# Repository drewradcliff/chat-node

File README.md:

# chat-node

A small USB-C-powered Wi-Fi voice puck for the kitchen or living room: one microphone, one speaker, one big
lit button. It is a thin audio client. It streams microphone audio to a gateway on a Mac mini over a
WebSocket and plays what the gateway streams back. No AI model and no third-party keys live on the device.

| Folder | What is in it |
|---|---|
| `boards/chat-node/` | KiCad project of the main board (schematic, layout, project library) and the scripts that generate it |
| `mfg/chat-node/` | Generated manufacturing set: Gerbers, drill, BOM, placement, schematic PDF, check reports. Never edit by hand |
| `mech/` | 3D-printed enclosure: FreeCAD scripts, STEP files, renders, fit-check log |
| `firmware/` | ESP-IDF firmware and the wire protocol (`PROTOCOL.md`). Not yet compiled or run on hardware |
| `gateway/` | Small Python bring-up server (echo and tone modes). Not the real gateway, no AI |

## Hardware in brief

- ESP32-S3-WROOM-1-N16R8 (16 MB flash, 8 MB PSRAM, built-in antenna), native USB for flashing and console.
- TDK ICS-43434 I2S microphone; MAX98357A I2S Class-D amplifier into a 40 mm, 4 ohm, 3 W speaker.
- Mic and amplifier are on separate I2S ports, so full duplex can be tried later without a board change.
- Kailh Choc V1 keyboard switch as the main button, lit from below by one SK6812MINI-E RGB LED.
- USB-C, 5 V only: 5.1k on each CC pin, 2 A resettable fuse, ESD array on the data lines, 3.3 V LDO.
- Board: 48 x 37 mm, 2 layers, all assembled parts on one side.

The board hangs under the lid with its component side facing DOWN. The bare back of the board faces the lid:
the microphone listens up through a hole in the board, the LED shines up through a slot, and the switch
stands on the back of the board under the button cap.

| Function | GPIO |
|---|---|
| Mic SCK / WS / SD (I2S0) | 11 / 13 / 14 |
| Amp SD_MODE / DIN / BCLK / LRCLK (I2S1) | 4 / 5 / 6 / 7 |
| Main button (to GND) | 15 |
| Status LED data | 16 |
| USB D- / D+ | 19 / 20 |
| BOOT button | 0 |
| Free | 8, 9, 10, 12, 17, 18 |

Test pads on the component side: 5V, 3V3, GND, EN, mic SD, mic SCK, amp DIN.

## The board files are generated

`chat-node.kicad_sch` and `chat-node.kicad_pcb` are written by scripts in `boards/chat-node/scripts/`.
Re-running them overwrites the KiCad files, so make changes in the scripts, or stop using the scripts once
you start editing in KiCad.

- `make_sch.py` draws the schematic; `layout.py` holds placement, tracks and vias; `make_pcb.py` builds the board.
- `scripts/build.sh sch` regenerates schematic, netlist and board. `scripts/build.sh` regenerates the board only.
- `scripts/export.sh` writes the manufacturing set to `mfg/chat-node/`.

## Parts to buy besides the board and the prints

| Part | Notes |
|---|---|
| Speaker | Same Sky CMS-4017-34SP (40 mm, 4 ohm, 3 W, solder tabs) |
| Main switch | Kailh Choc V1 (PG1350), any variant; a quiet linear one suits a kitchen |
| Speaker lead | 2-pin JST PH plug with wires, soldered to the speaker tabs |
| Screws | 3x M2 x 5 thread-forming (board), 4x M2.5 x 8 thread-forming countersunk (base) |
| Small parts | 1 mm foam pad behind the speaker magnet, a thin foam ring for the microphone port, 4 stick-on feet (8 mm) |

## Assembly

1. Push the Choc switch into the BACK of the board (the side without parts) and solder its two pins on the component side.
2. Solder the JST PH lead to the speaker tabs.
3. Turn the shell upside down. Drop the button cap into its hole from inside.
4. Put the foam ring on the microphone boss. Lower the board in, component side toward you, so the switch stem
   enters the cap; fasten with three M2 screws.
5. Put the speaker with its gasket into the ring under the grille, tabs toward the back. Lead the wires through
   the notch in the partition, plug them into J2, and seal the notch with a dab of glue or foam.
6. Stick the foam pad on the base's speaker pad. Hook the base's right edge in first, swing it shut, four screws, feet.

Flashing, provisioning and the bring-up tests (LED, button, speaker tone, mic level, loopback) are in
`firmware/README.md`. RESET and BOOT are on the component side and are reachable with the base off.

## Check before ordering

- The Choc switch heights and stem slots used for the button cap are nominal values, not measured: compare
  `mech/params.py` with a real switch, and test-print the cap.
- The fab's assembly preview: confirm part rotations, above all U1, U2, U3, J1, D1 (reverse mount) and MK1.
- The firmware has not been built. `firmware/README.md` lists the places most likely to need a fix.

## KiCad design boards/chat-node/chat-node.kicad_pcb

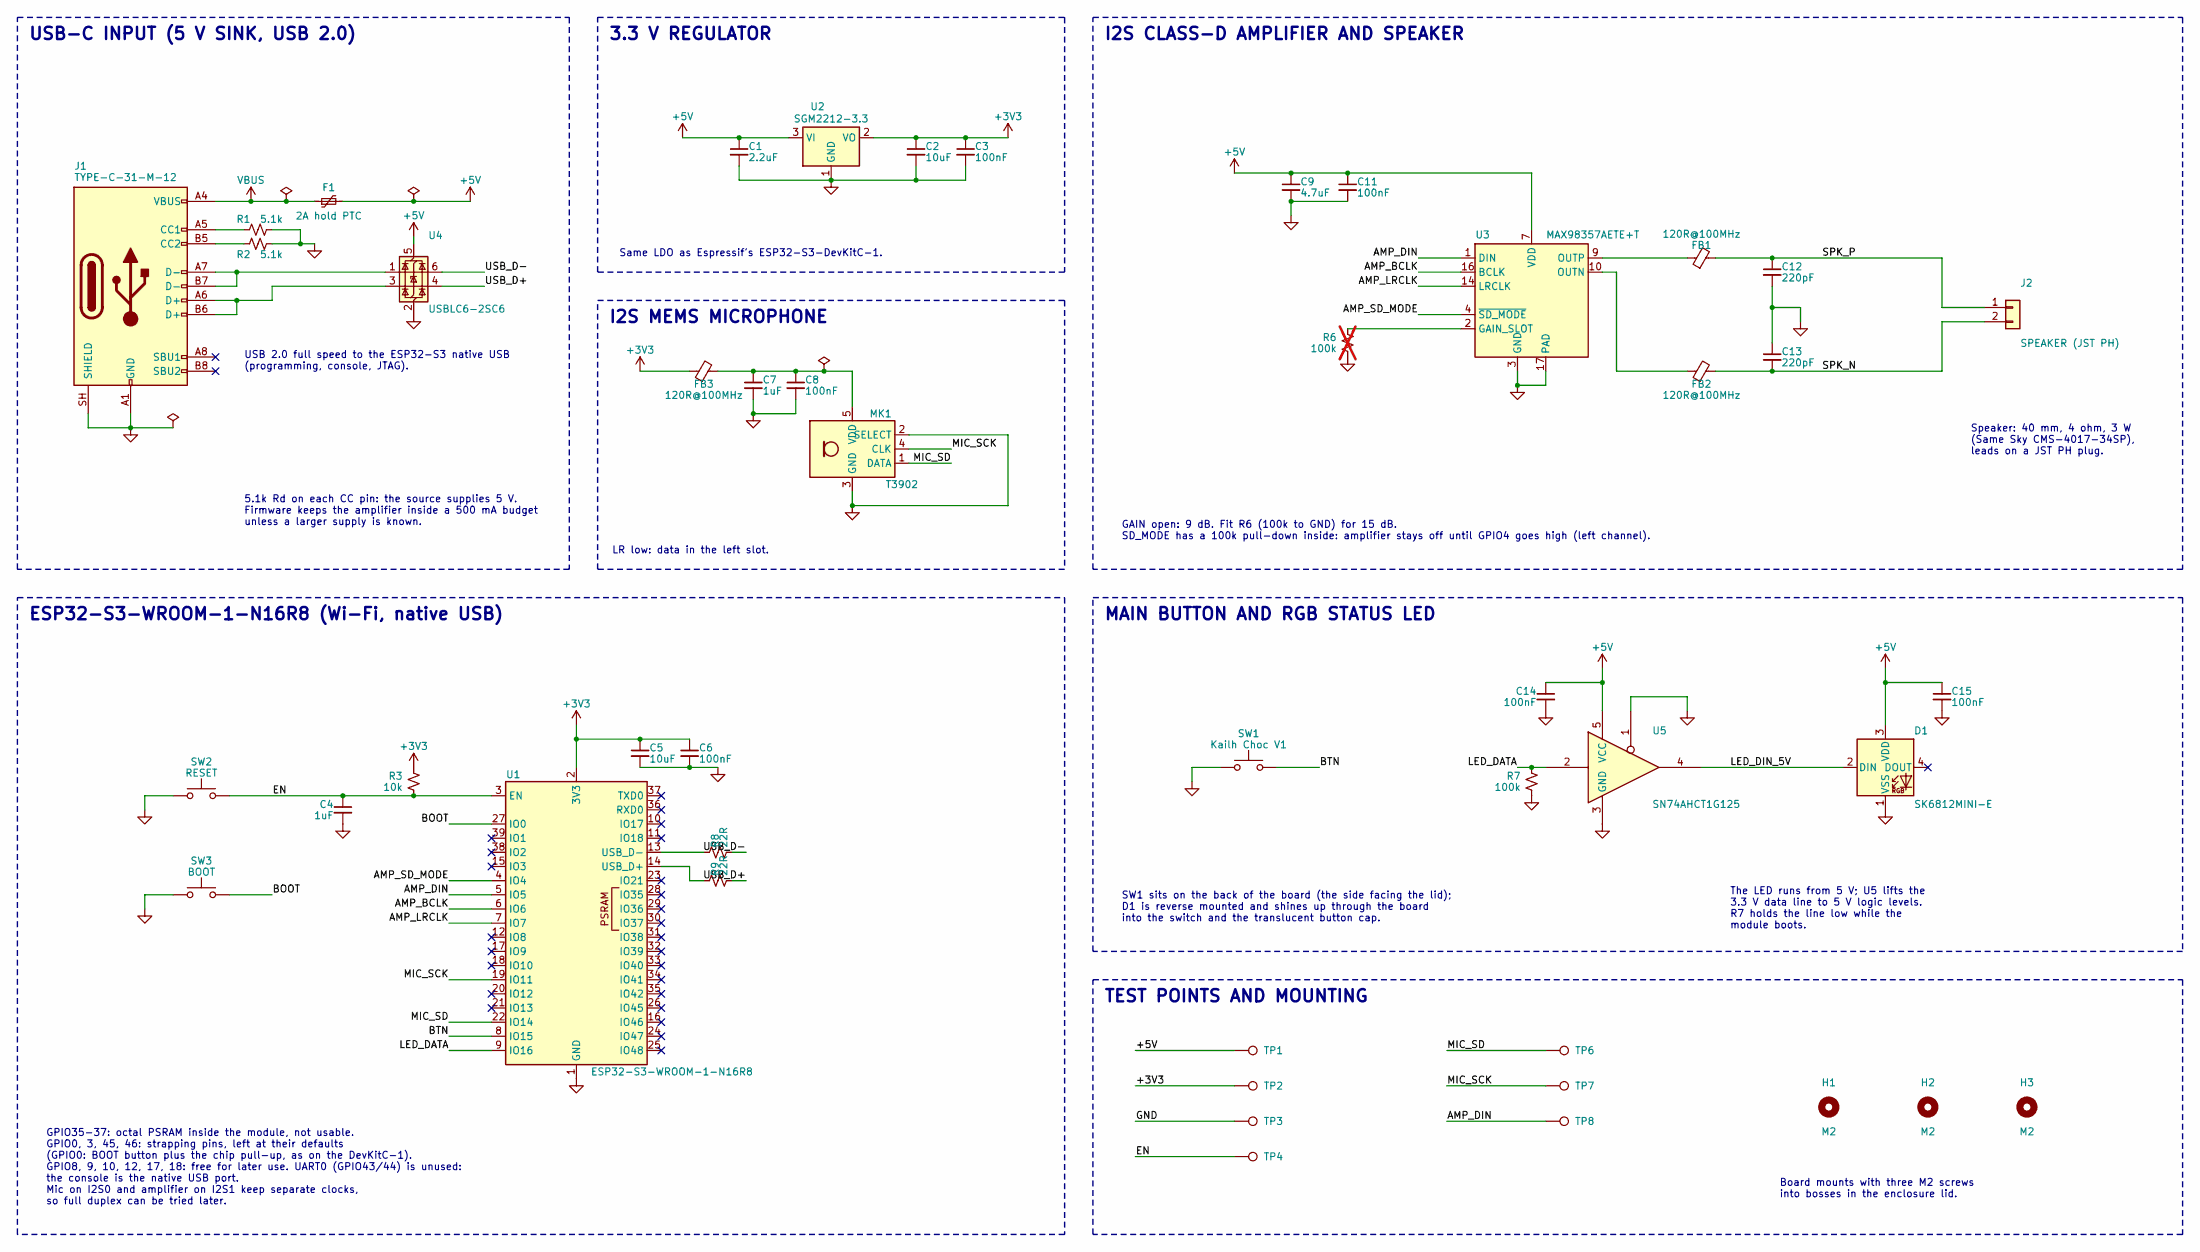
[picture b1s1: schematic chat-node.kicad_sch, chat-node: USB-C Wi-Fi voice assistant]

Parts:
C1: 2.2uF; C_0805_2012Metric; MPN CL21A225KBQNNNE; LCSC C377773
C2, C5: 10uF; C_0805_2012Metric; MPN CL21A106KAYNNNE; LCSC C15850
C3, C6, C8, C11, C14, C15: 100nF; C_0402_1005Metric; MPN CL05B104KO5NNNC; LCSC C1525
C4, C7: 1uF; C_0402_1005Metric; MPN CL05A105KA5NQNC; LCSC C52923
C9: 4.7uF; C_0805_2012Metric; MPN CL21A475KAQNNNE; LCSC C1779
C12, C13: 220pF; C_0402_1005Metric; MPN GRM1555C1H221JA01D; LCSC C71693
D1: SK6812MINI-E; LED_SK6812MINI-E_3.2x2.8mm_P1.5mm_ReverseMount; MPN SK6812MINI-E; LCSC C5149201
F1: 2A hold PTC; Fuse_1206_3216Metric; MPN BSMD1206-200-16V; LCSC C2685749
FB1, FB2, FB3: 120R@100MHz; L_0805_2012Metric; MPN HCB2012KF-121T50; LCSC C304323
H1, H2, H3: M2; MountingHole_2.2mm_M2
J1: TYPE-C-31-M-12; USB_C_Receptacle_HRO_TYPE-C-31-M-12; MPN TYPE-C-31-M-12; LCSC C165948
J2: SPEAKER (JST PH); JST_PH_B2B-PH-SM4-TB_1x02-1MP_P2.00mm_Vertical; MPN B2B-PH-SM4-TB(LF)(SN); LCSC C160352
MK1: T3902; TDK_T3902_LGA-5_3.5x2.65mm; MPN MMICT3902-00-012; LCSC C3171752
R1, R2: 5.1k; R_0402_1005Metric; MPN 0402WGF5101TCE; LCSC C25905
R3: 10k; R_0402_1005Metric; MPN 0402WGF1002TCE; LCSC C25744
R6: 100k; R_0402_1005Metric; MPN 0402WGF1003TCE; LCSC C25741; not fitted
R7: 100k; R_0402_1005Metric; MPN 0402WGF1003TCE; LCSC C25741
R8, R9: 22R; R_0402_1005Metric; MPN 0402WGF220JTCE; LCSC C25092
SW1: Kailh Choc V1; SW_Kailh_Choc_V1_Reverse; MPN CPG135001D01
SW2: RESET; SW_Push_1P1T_XKB_TS-1187A; MPN TS-1187A-B-A-B; LCSC C318884
SW3: BOOT; SW_Push_1P1T_XKB_TS-1187A; MPN TS-1187A-B-A-B; LCSC C318884
TP1: +5V; TestPoint_Pad_D1.0mm
TP2: +3V3; TestPoint_Pad_D1.0mm
TP3: GND; TestPoint_Pad_D1.0mm
TP4: EN; TestPoint_Pad_D1.0mm
TP6: MIC_SD; TestPoint_Pad_D1.0mm
TP7: MIC_SCK; TestPoint_Pad_D1.0mm
TP8: AMP_DIN; TestPoint_Pad_D1.0mm
U1: ESP32-S3-WROOM-1-N16R8; ESP32-S3-WROOM-1; MPN ESP32-S3-WROOM-1-N16R8; LCSC C2913202
U2: SGM2212-3.3; SOT-223-3_TabPin2; MPN SGM2212-3.3XKC3G/TR; LCSC C3294699
U3: MAX98357AETE+T; TQFN-16-1EP_3x3mm_P0.5mm_EP1.23x1.23mm; MPN MAX98357AETE+T; LCSC C910544
U4: USBLC6-2SC6; SOT-23-6; MPN USBLC6-2SC6; LCSC C7519
U5: SN74AHCT1G125; SOT-23-5; MPN SN74AHCT1G125DBVR; LCSC C7484

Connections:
+3V3: C2.1, C3.1, C5.1, C6.1, FB3.1, R3.1, TP2.1 (1_1), U1.2 (3V3), U2.2 (VO)
+5V: C1.1, C9.1, C11.1, C14.1, C15.1, D1.3 (VDD), F1.2, TP1.1 (1_1), U2.3 (VI), U3.7 (VDD), U3.8 (VDD), U4.5 (VBUS), U5.5 (VCC)
/AMP_BCLK: U1.6 (IO6), U3.16 (BCLK)
/AMP_DIN: TP8.1 (1_1), U1.5 (IO5), U3.1 (DIN)
/AMP_LRCLK: U1.7 (IO7), U3.14 (LRCLK)
/AMP_SD_MODE: U1.4 (IO4), U3.4 (~SD_MODE)
/BOOT: SW3.2, U1.27 (IO0)
/BTN: SW1.2, U1.8 (IO15)
/EN: C4.1, R3.2, SW2.2, TP4.1 (1_1), U1.3 (EN)
/LED_DATA: R7.1, U1.9 (IO16), U5.2
/LED_DIN_5V: D1.2 (DIN), U5.4
/MIC_SCK: MK1.4 (CLK), TP7.1 (1_1), U1.19 (IO11)
/MIC_SD: MK1.1 (DATA), TP6.1 (1_1), U1.22 (IO14)
/SPK_N: C13.2, FB2.2, J2.2
/SPK_P: C12.1, FB1.2, J2.1
/USB_D+: R9.2, U4.4 (I/O2)
/USB_D-: R8.2, U4.6 (I/O1)
GND: C1.2, C2.2, C3.2, C4.2, C5.2, C6.2, C7.2, C8.2, C9.2, C11.2, C12.2, C13.1, C14.2, C15.2, D1.1 (VSS), J1.A1 (GND), J1.A12 (GND), J1.B1 (GND), J1.B12 (GND), J1.SH (SHIELD), MK1.2 (SELECT), MK1.3 (GND), R1.2, R2.2, R6.2, R7.2, SW1.1, SW2.1, SW3.1, TP3.1 (1_1), U1.1 (GND), U1.40 (GND), U1.41 (GND), U2.1 (GND), U3.3 (GND), U3.11 (GND), U3.15 (GND), U3.17 (PAD), U4.2 (GND), U5.1, U5.3 (GND)
unnamed: J1.A5 (CC1), R1.1
unnamed: J1.B5 (CC2), R2.1
unnamed: J1.A6 (D+), J1.B6 (D+), U4.3 (I/O2)
unnamed: J1.A7 (D-), J1.B7 (D-), U4.1 (I/O1)
unnamed: C7.1, C8.1, FB3.2, MK1.5 (VDD)
unnamed: R9.1, U1.14 (USB_D+)
unnamed: R8.1, U1.13 (USB_D-)
unnamed: R6.1, U3.2 (GAIN_SLOT)
unnamed: FB2.1, U3.10 (OUTN)
unnamed: FB1.1, U3.9 (OUTP)
VBUS: F1.1, J1.A4 (VBUS), J1.A9 (VBUS), J1.B4 (VBUS), J1.B9 (VBUS)

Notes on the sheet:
SW1 sits on the back of the board (the side facing the lid); D1 is reverse mounted and shines up through the board into the switch and the translucent button cap.
Same LDO as Espressif's ESP32-S3-DevKitC-1.
GPIO35-37: octal PSRAM inside the module, not usable. GPIO0, 3, 45, 46: strapping pins, left at their defaults (GPIO0: BOOT button plus the chip pull-up, as on the DevKitC-1). GPIO8, 9, 10, 12, 17, 18: free for later use. UART0 (GPIO43/44) is unused: the console is the native USB port. Mic on I2S0 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
MAIN BUTTON AND RGB STATUS LED
GAIN open: 9 dB. Fit R6 (100k to GND) for 15 dB. SD_MODE has a 100k pull-down inside: amplifier stays off until GPIO4 goes high (left channel).
TEST POINTS AND MOUNTING
LR low: data in the left slot.
I2S MEMS MICROPHONE
Board mounts with three M2 screws into bosses in the enclosure lid.
The LED runs from 5 V; U5 lifts the 3.3 V data line to 5 V logic levels. R7 holds the line low while the module boots.
Speaker: 40 mm, 4 ohm, 3 W (Same Sky CMS-4017-34SP), leads on a JST PH plug.
5.1k Rd on each CC pin: the source supplies 5 V. Firmware keeps the amplifier inside a 500 mA budget unless a larger supply is known.
USB 2.0 full speed to the ESP32-S3 native USB (programming, console, JTAG).
3.3 V REGULATOR
USB-C INPUT (5 V SINK, USB 2.0)
I2S CLASS-D AMPLIFIER AND SPEAKER
ESP32-S3-WROOM-1-N16R8 (Wi-Fi, native USB)

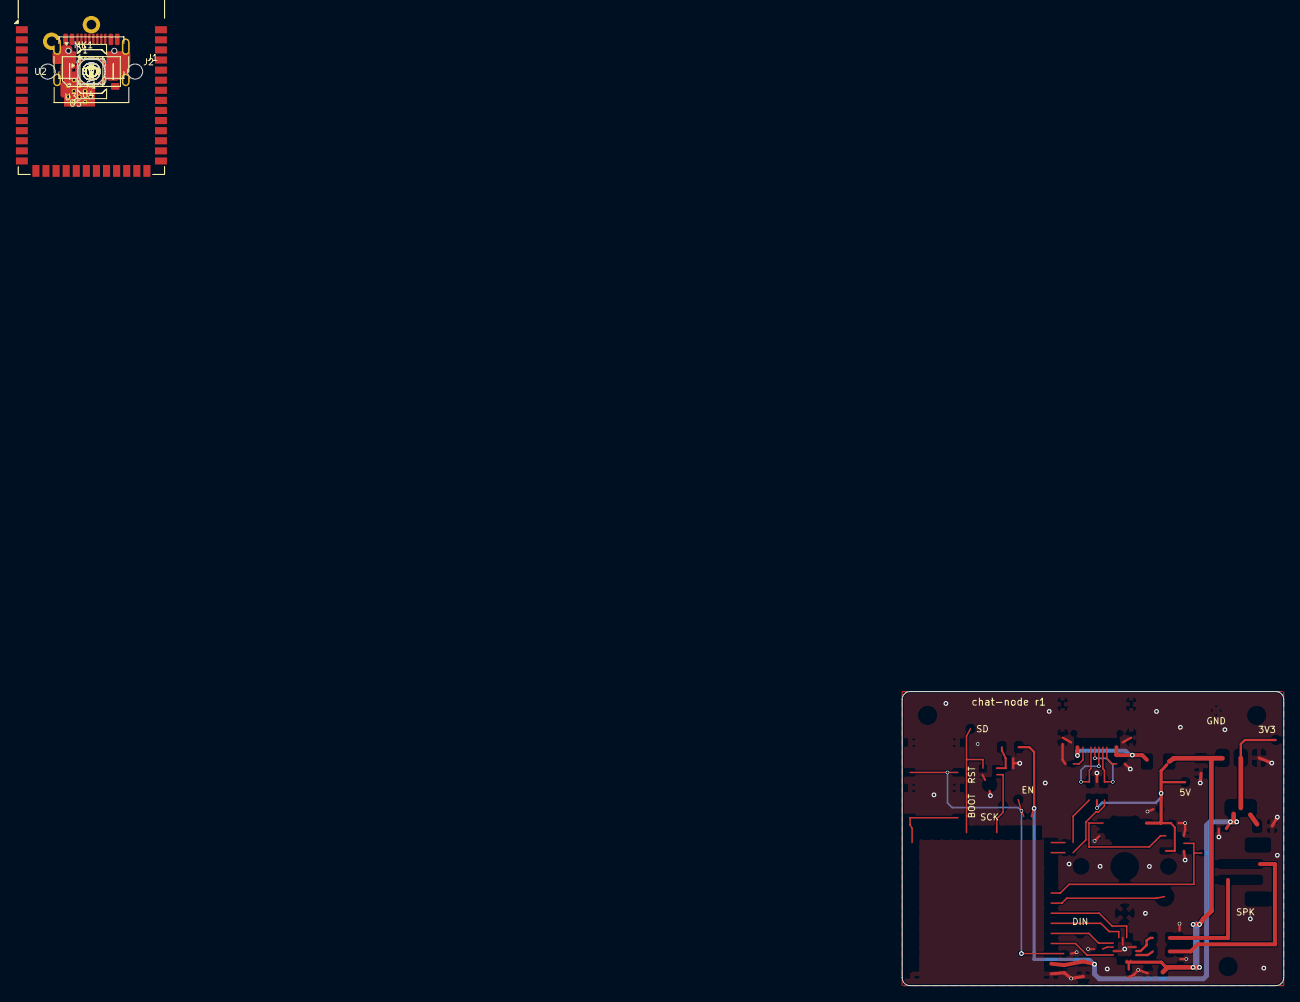
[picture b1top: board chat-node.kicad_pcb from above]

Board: 2 copper layers, 3.6 x 3.2 mm, 47 parts (0 on the bottom side), 29 nets.

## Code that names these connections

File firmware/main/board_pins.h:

// Every GPIO used by chat-node lives here; no other file names a pin number.
// Module: ESP32-S3-WROOM-1-N16R8. Pin map is final as of the routed PCB.
//
// Reserved, never use:
//   GPIO0      BOOT strapping button (chip's internal pull-up only, no external
//              resistor); firmware leaves it alone
//   GPIO19/20  native USB D-/D+: the only console and programming port
//   GPIO35-37  octal PSRAM
// UART0 (GPIO43/44) is not brought out on this board.
// Spare, unconnected: GPIO8, GPIO9, GPIO10, GPIO12, GPIO17, GPIO18.
#pragma once

#include "driver/gpio.h"
#include "driver/i2s_types.h"

// Microphone: TDK ICS-43434, I2S0 RX only, LR tied to GND -> data in LEFT slot.
#define MIC_I2S_PORT        I2S_NUM_0
#define PIN_MIC_SCK         GPIO_NUM_11
#define PIN_MIC_WS          GPIO_NUM_13
#define PIN_MIC_SD          GPIO_NUM_14

// Amplifier: MAX98357A, I2S1 TX only, no MCLK.
#define AMP_I2S_PORT        I2S_NUM_1
#define PIN_AMP_DIN         GPIO_NUM_5
#define PIN_AMP_BCLK        GPIO_NUM_6
#define PIN_AMP_LRCLK       GPIO_NUM_7
// High = amp on (left channel). Low/Hi-Z = shutdown (100k pull-down inside the
// amp keeps it off through boot).
#define PIN_AMP_SD_MODE     GPIO_NUM_4

// Main button: key switch to GND, active low, internal pull-up. RTC-capable.
#define PIN_BUTTON          GPIO_NUM_15

// Status LED: SK6812MINI-E through a non-inverting 74AHCT1G125 buffer.
#define PIN_LED_DATA        GPIO_NUM_16

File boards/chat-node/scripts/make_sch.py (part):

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s.stub(MK1.p(4), 7.62, 'MIC_SCK', CMIC)
sd = MK1.p(6)
s.wire(sd, (190.5, sd[1]), color=CMIC)
s.label('MIC_SD', (190.5, sd[1]), 0, CMIC)
R5 = R('R5', '100k', 185.42, sd[1] + 2.54, side='r')
s.junction(R5.p(1), CMIC)
s.pwr('GND', R5.p(2))
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s.wire((330.2, 69.85), (335.28, 69.85), (335.28, 72.39))
s.junction((330.2, 69.85))
s.pwr('GND', (335.28, 72.39))
s.label('SPK_P', (339.09, op[1]), 0, CSPK)
s.label('SPK_N', (339.09, yn), 0, CSPK)
s.text('GAIN open: 9 dB. Fit R6 (100k to GND) for 15 dB.\n'
       'SD_MODE has a 100k pull-down inside: amplifier stays off until GPIO4 goes high (left channel).',
       213.36, 111.76, size=1.27)
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           props=dict(MPN='SK6812MINI-E', Manufacturer='OPSCO Optoelectronics', LCSC='C5149201'),
           ref_at=(5.08, -6.6, 'left'), val_at=(5.08, 6.6, 'left'))
s.wire(U5.p(4), D1.p(2), color=CLED)
s.label('LED_DIN_5V', (322.58, 152.4), 0, CLED)
s.nc(D1.p(4))
dv = D1.p(3)
s.wire(dv, (dv[0], 134.62), color=C5V)
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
